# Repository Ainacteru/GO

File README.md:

# The GO flight computer
### What is this?
This repository contains the most if not all files for what is in and on the flight computer. 
### Why?
Trying to improve on working on the hardware design of embedded systems, and also learning Rust at the same time
### About the board:
Hardware:
* MCU: ATSAMD21G18A-AU
* IMU: BMI323
* Barometer: BMP390
* Flash: W25Q16JVSSIQ
* Radio: Wio-SX1262
* Buzzer
* RGB Led
* 3 Servo Ports
* 2 Pyro Channels
* USB-C
* Micro-SD card reader

Runs off of the [Microsoft UF2-SAMDx1](https://github.com/microsoft/uf2-samdx1) UF2 flashing bootloader

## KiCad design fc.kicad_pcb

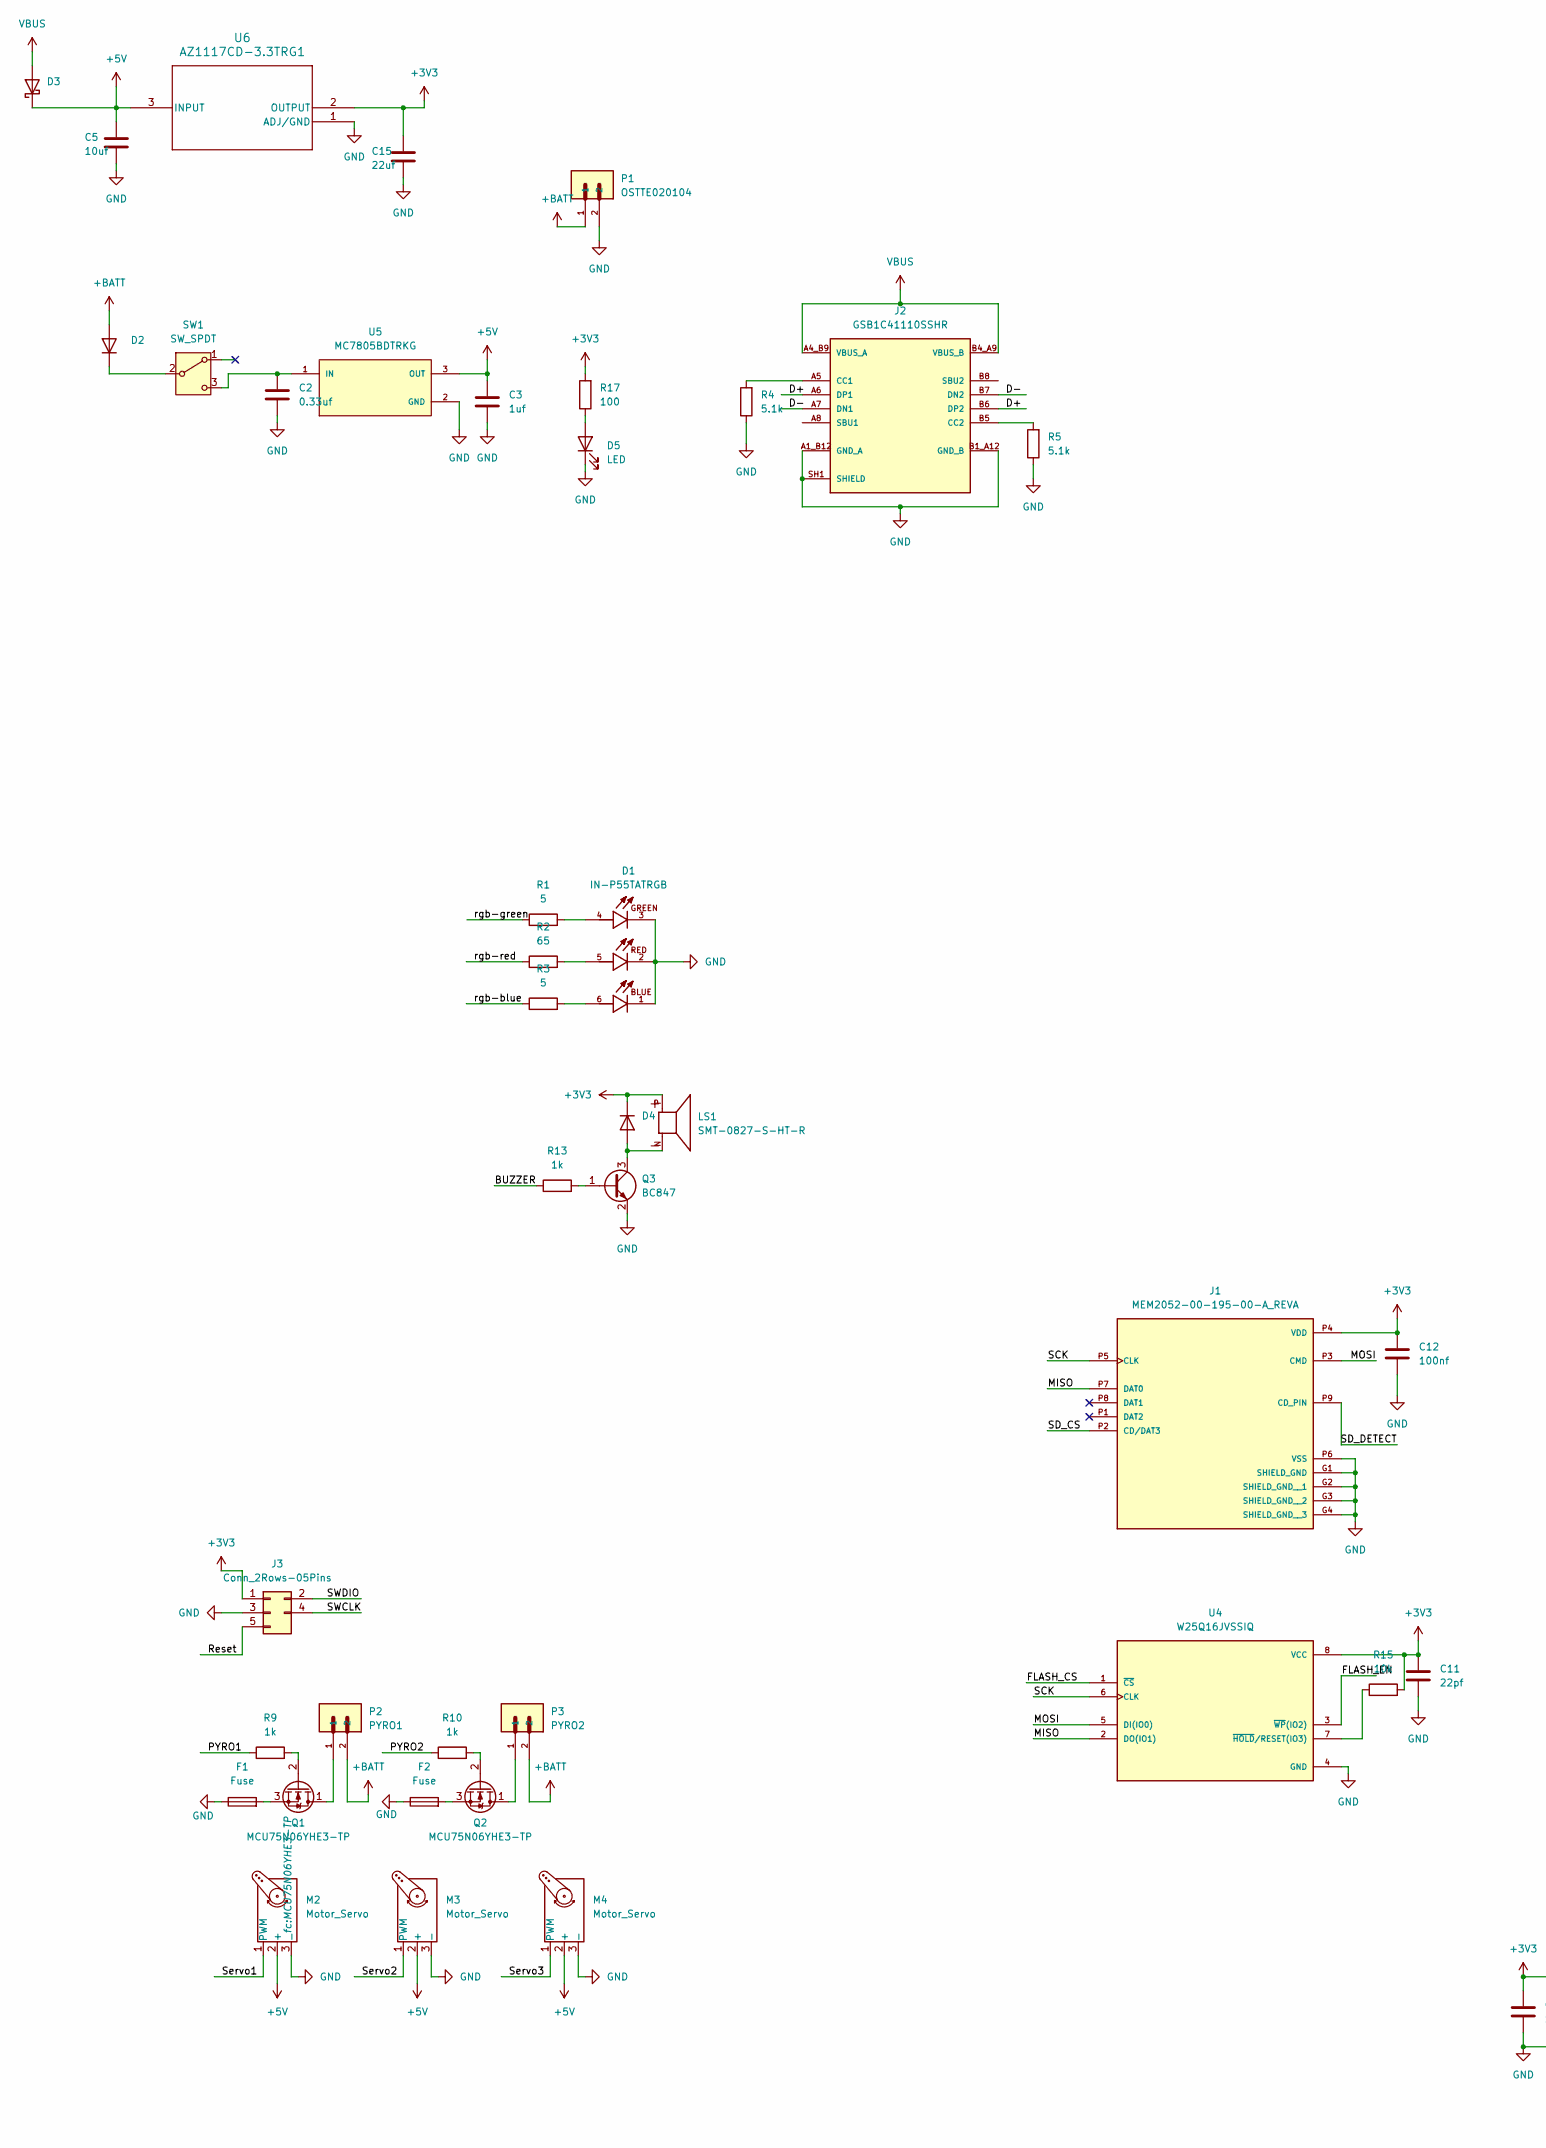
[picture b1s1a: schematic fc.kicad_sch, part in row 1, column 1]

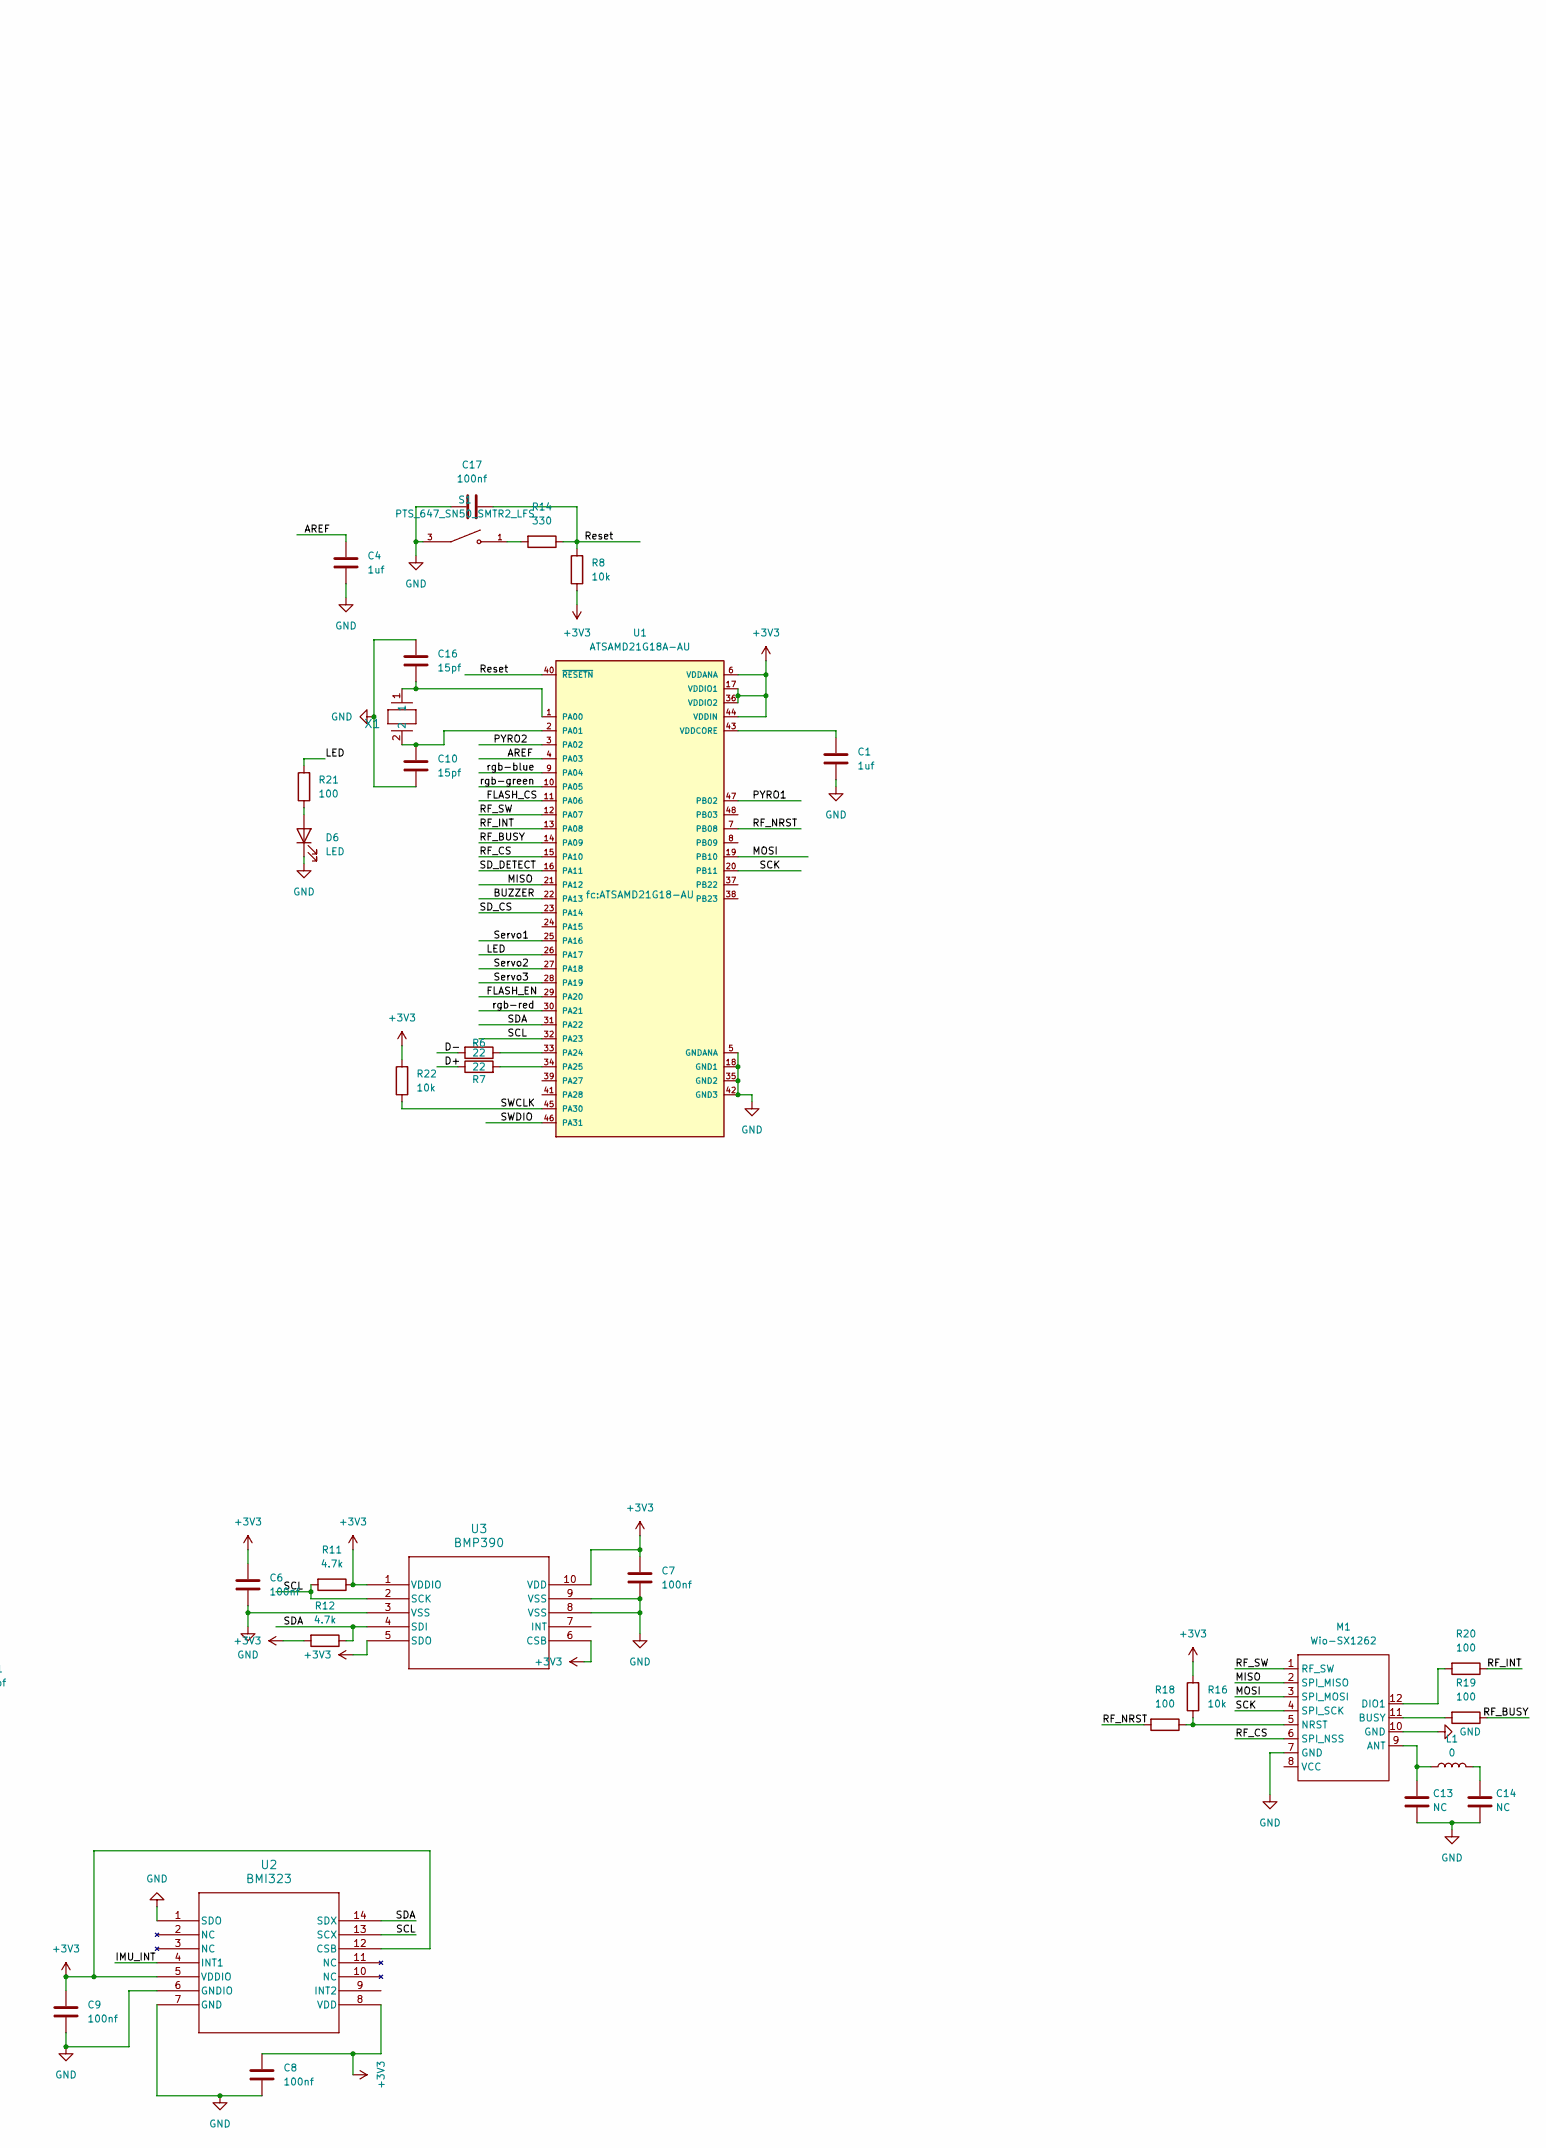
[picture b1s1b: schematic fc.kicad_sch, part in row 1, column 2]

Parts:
C1, C3, C4: 1uf; 0603-cap
C2: 0.33uf; 0603-cap
C5: 10uf; 0603-cap
C6, C7, C8, C9, C12, C17: 100nf; 0603-cap
C10, C16: 15pf; 0603-cap
C11: 22pf; 0603-cap
C13, C14: NC; C_0402_1005Metric
C15: 22uf; 0603-cap
D1: IN-P55TATRGB; LED_IN-P55TATRGB; PARTREV 1.0
D2, D3, D4: D_SOD-123
D5, D6: LED; LED_0603_1608Metric
F1, F2: Fuse; Fuse_0603_1608Metric
J1: MEM2052-00-195-00-A_REVA; GCT_MEM2052-00-195-00-A_REVA; PARTREV A
J2: GSB1C41110SSHR; AMPHENOL_GSB1C41110SSHR; PARTREV AX1; DigiKey_Part_Number 664-GSB1C41110SSHRCT-ND
J3: Conn_2Rows-05Pins; PinSocket_2x03_odd
L1: 0; L_0402_1005Metric
LS1: SMT-0827-S-HT-R; XDCR_SMT-0827-S-HT-R; PARTREV 31/03/20
M1: Wio-SX1262
M2, M3, M4: Motor_Servo; PinHeader_1x03_P2.54mm_Vertical
P1: OSTTE020104; OST_OSTTE020104
P2: PYRO1; OST_OSTTE020104
P3: PYRO2; OST_OSTTE020104
Q1, Q2: MCU75N06YHE3-TP
Q3: BC847; SOT-23
R1, R3: 5; R_0603_1608Metric
R2: 65; R_0603_1608Metric
R4, R5: 5.1k; R_0603_1608Metric
R6, R7: 22; R_0603_1608Metric
R8, R15, R16, R22: 10k; R_0603_1608Metric
R9, R10, R13: 1k; R_0603_1608Metric
R11, R12: 4.7k; R_0603_1608Metric
R14: 330; R_0603_1608Metric
R17, R18, R19, R20, R21: 100; R_0603_1608Metric
S1: PTS_647_SN50_SMTR2_LFS; SW_PTS_647_SN50_SMTR2_LFS; PARTREV 4 Apr 22
SW1: SW_SPDT; SW_OS102011MS2QN1
U1: ATSAMD21G18A-AU; ATSAMD21G18-AU
U2: BMI323; BMI323_BOS
U3: BMP390
U4: W25Q16JVSSIQ
U5: MC7805BDTRKG; DPAK229P990X238-4N; PARTREV 27
U6: AZ1117CD-3.3TRG1; TO252-2-3.3V_DIO
X1: FC-135 32.7680KA-A5; XTAL_FC-135_EPS

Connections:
+3V3: C6.1, C7.1, C8.1, C9.1, C11.1, C12.1, C15.1, D4.1 (K), J1.P4 (VDD), J3.1, LS1.P, R8.1, R11.1, R12.2, R15.2, R16.2, R17.2, R22.2, U1.6 (VDDANA), U1.17 (VDDIO1), U1.36 (VDDIO2), U1.44 (VDDIN), U2.5 (VDDIO), U2.8 (VDD), U2.12 (CSB), U3.1 (VDDIO), U3.5 (SDO), U3.6 (CSB), U3.10 (VDD), U4.8 (VCC), U6.2 (OUTPUT)
+5V: C3.1, C5.1, D3.1 (K), M2.2 (+), M3.2 (+), M4.2 (+), U5.3 (OUT), U6.3 (INPUT)
+BATT: D2.2 (A), P1.1, P2.2, P3.2
/AREF: C4.1, U1.4 (PA03)
/BUZZER: R13.1, U1.22 (PA13)
/FLASH_CS: U1.11 (PA06), U4.1 (~CS)
/FLASH_EN: U1.29 (PA20), U4.3 (~WP(IO2))
/IMU_INT: U2.4 (INT1)
/LED: R21.2, U1.26 (PA17)
/MISO: J1.P7 (DAT0), M1.2 (SPI_MISO), U1.21 (PA12), U4.2 (DO(IO1))
/MOSI: J1.P3 (CMD), M1.3 (SPI_MOSI), U1.19 (PB10), U4.5 (DI(IO0))
/PYRO1: R9.1, U1.47 (PB02)
/PYRO2: R10.1, U1.3 (PA02)
/RF_BUSY: R19.1, U1.14 (PA09)
/RF_CS: M1.6 (SPI_NSS), U1.15 (PA10)
/RF_INT: R20.1, U1.13 (PA08)
/RF_NRST: R18.2, U1.7 (PB08)
/RF_SW: M1.1 (RF_SW), U1.12 (PA07)
/Reset: C17.2, J3.5, R8.2, R14.1, U1.40 (~RESETN)
/SCK: J1.P5 (CLK), M1.4 (SPI_SCK), U1.20 (PB11), U4.6 (CLK)
/SCL: R11.2, U1.32 (PA23), U2.13 (SCX), U3.2 (SCK)
/SDA: R12.1, U1.31 (PA22), U2.14 (SDX), U3.4 (SDI)
/SD_CS: J1.P2 (CD/DAT3), U1.23 (PA14)
/SD_DETECT: J1.P9 (CD_PIN), U1.16 (PA11)
/SWCLK: J3.4, R22.1, U1.45 (PA30)
/SWDIO: J3.2, U1.46 (PA31)
/Servo1: M2.1 (PWM), U1.25 (PA16)
/Servo2: M3.1 (PWM), U1.27 (PA18)
/Servo3: M4.1 (PWM), U1.28 (PA19)
/rgb-blue: R3.1, U1.9 (PA04)
/rgb-green: R1.1, U1.10 (PA05)
/rgb-red: R2.1, U1.30 (PA21)
GND: C1.2, C2.2, C3.2, C4.2, C5.2, C6.2, C7.2, C8.2, C9.2, C10.1, C11.2, C12.2, C13.2, C14.2, C15.2, C16.1, C17.1, D1.1, D1.2, D1.3, D5.1 (K), D6.1 (K), F1.1, F2.1, J1.G1 (SHIELD_GND), J1.G2 (SHIELD_GND__1), J1.G3 (SHIELD_GND__2), J1.G4 (SHIELD_GND__3), J1.P6 (VSS), J2.A1_B12 (GND_A), J2.B1_A12 (GND_B), J2.SH1 (SHIELD), J2.SH2 (SHIELD), J2.SH3 (SHIELD), J2.SH4 (SHIELD), J3.3, M1.7 (GND), M1.10 (GND), M2.3 (-), M3.3 (-), M4.3 (-), P1.2, Q3.2 (E), R4.1, R5.1, S1.3, S1.4, U1.5 (GNDANA), U1.18 (GND1), U1.35 (GND2), U1.42 (GND3), U2.1 (SDO), U2.6 (GNDIO), U2.7 (GND), U3.3 (VSS), U3.8 (VSS), U3.9 (VSS), U4.4 (GND), U5.2 (GND), U6.1 (ADJ/GND)
unnamed: C14.1, L1.2
unnamed: D1.4, R1.2
unnamed: D1.5, R2.2
unnamed: D1.6, R3.2
unnamed: D2.1 (K), SW1.2 (B)
unnamed: D4.2 (A), LS1.N, Q3.3 (C)
unnamed: D5.2 (A), R17.1
unnamed: D6.2 (A), R21.1
unnamed: J2.A5 (CC1), R4.2
unnamed: J2.B5 (CC2), R5.2
unnamed: C13.1, L1.1, M1.9 (ANT)
unnamed: M1.11 (BUSY), R19.2
unnamed: M1.12 (DIO1), R20.2
unnamed: M1.5 (NRST), R16.1, R18.1
unnamed: P2.1, Q1.1 (D)
unnamed: Q1.2 (G), R9.2
unnamed: F1.2, Q1.3 (S)
unnamed: P3.1, Q2.1 (D)
unnamed: Q2.2 (G), R10.2
unnamed: F2.2, Q2.3 (S)
unnamed: Q3.1 (B), R13.2
unnamed: R14.2, S1.1, S1.2
unnamed: C2.1, SW1.3 (C), U5.1 (IN)
unnamed: C16.2, U1.1 (PA00), X1.1
unnamed: C10.2, U1.2 (PA01), X1.2
unnamed: R6.1, U1.33 (PA24)
unnamed: R7.2, U1.34 (PA25)
unnamed: C1.1, U1.43 (VDDCORE)
unnamed: R15.1, U4.7 (~HOLD/RESET(IO3))
VBUS: D3.2 (A), J2.A4_B9 (VBUS_A), J2.B4_A9 (VBUS_B)

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
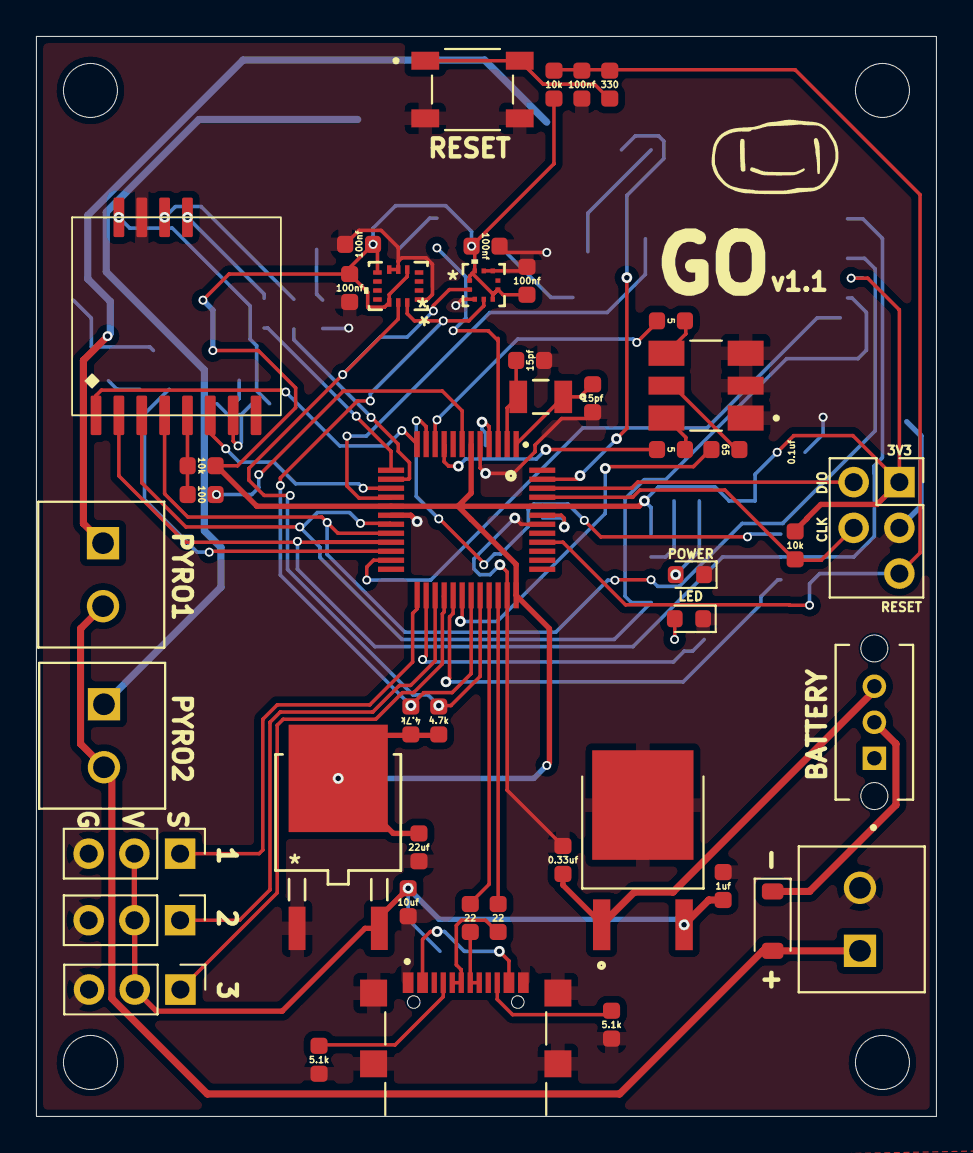
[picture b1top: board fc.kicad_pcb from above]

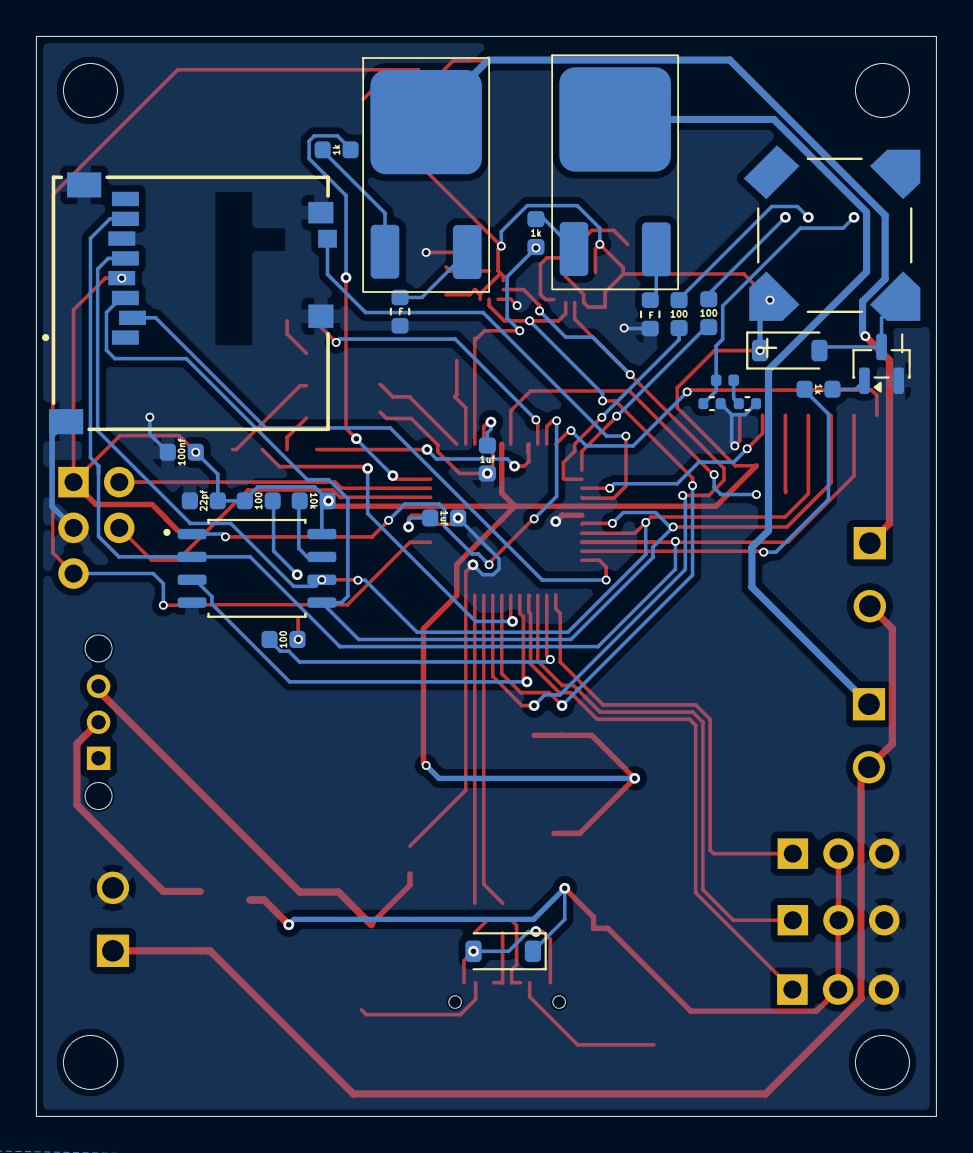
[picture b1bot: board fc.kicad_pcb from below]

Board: 2 copper layers, 50.0 x 60.0 mm, 71 parts (25 on the bottom side), 64 nets.

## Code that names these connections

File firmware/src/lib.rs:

#![no_std]


pub mod communcation;
pub mod actuators;
pub mod indicators;
pub mod sensors;
pub mod peripherals;

#[cfg(feature = "rt")]
pub use cortex_m_rt::entry;

pub use atsamd_hal as hal;
pub use hal::ehal;
pub use hal::pac;

use hal::clock::GenericClockController;
use hal::sercom::{i2c, spi};
use hal::time::Hertz;

#[cfg(feature = "usb")]
use hal::usb::{usb_device::bus::UsbBusAllocator, UsbBus};

hal::bsp_peripherals!(
    Sercom3 { I2cSercom }
    Sercom4 { SpiSercom }
);

/// Definitions related to pins and pin aliases
pub mod pins {
    use super::hal;

    hal::bsp_pins!(
        PA02 {
            /// Pyro channel 2 output
            name: pyro2
            aliases: {
                PushPullOutput: Pyro2
            }
        }
        PA03 {
            /// AREF pin - has 1uF capacitor to ground
            name: aref
        }
        PA04 {
            /// RGB LED blue channel
            name: rgb_blue
            aliases: {
                PushPullOutput: RgbBlue
                AlternateE: RgbBluePwm

            }
        }
        PA05 {
            /// RGB LED green channel
            name: rgb_green
            aliases: {
                PushPullOutput: RgbGreen
                AlternateE: RgbGreenPwm
            }
        }
        PA06 {
            /// SPI chip select for external flash
            name: flash_cs
            aliases: {
                PushPullOutput: FlashCs
            }
        }
        PA07 {
            /// RF module antenna switch
            name: rf_sw
            aliases: {
                PushPullOutput: RfSw
            }
        }
        PA08 {
            /// RF module interrupt
            name: rf_int
            aliases: {
                PullUpInput: RfInt
            }
        }
        PA09 {
            /// RF module busy signal
            name: rf_busy
            aliases: {
                PullUpInput: RfBusy
            }
        }
        PA10 {
            /// RF module chip select
            name: rf_cs
            aliases: {
                PushPullOutput: RfCs
            }
        }
        PA11 {
            /// SD card detect
            name: sd_detect
            aliases: {
                PullUpInput: SdDetect
            }
        }
        PA12 {
            /// SPI MISO
            name: miso
            aliases: {
                AlternateD: Miso
            }
        }
        PA13 {
            /// Buzzer output
            name: buzzer
            aliases: {
                PushPullOutput: Buzzer
            }
        }
        PA14 {
            /// SD card chip select
            name: sd_cs
            aliases: {
                PushPullOutput: SdCs
            }
        }
        PA16 {
            /// Servo 1 PWM output
            name: servo1
            aliases: {
                AlternateE: Servo1Pwm
            }
        }
        PA17 {
            /// Status LED
            name: led
            aliases: {
                PushPullOutput: Led
            }
        }
        PA18 {
            /// Servo 2 PWM output
            name: servo2
            aliases: {
                AlternateF: Servo2Pwm
            }
        }
        PA19 {
            /// Servo 3 PWM output
            name: servo3
            aliases: {
                AlternateF: Servo3Pwm
            }
        }
        PA20 {
            /// External flash enable
            name: flash_en
            aliases: {
                PushPullOutput: FlashEn
            }
        }
        PA21 {
            /// RGB LED red channel
            name: rgb_red
            aliases: {
                PushPullOutput: RgbRed
                AlternateF: RgbRedPwm
            }
        }
        PA22 {
            /// I2C data line
            name: sda
            aliases: {
                AlternateC: Sda
            }
        }
        PA23 {
            /// I2C clock line
            name: scl
            aliases: {
                AlternateC: Scl
            }
        }
        PA24 {
            /// USB D-
            name: usb_dm
            aliases: {
                AlternateG: UsbDm
            }
        }
        PA25 {
            /// USB D+
            name: usb_dp
            aliases: {
                AlternateG: UsbDp
            }
        }
        PB02 {
            /// Pyro channel 1 output
            name: pyro1
            aliases: {
                PushPullOutput: Pyro1
            }
        }
        PB08 {
            /// RF module reset
            name: rf_nrst
            aliases: {
                PushPullOutput: RfNrst
            }
        }
        PB10 {
            /// SPI MOSI
            name: mosi
            aliases: {
                AlternateD: Mosi
            }
        }
        PB11 {
            /// SPI SCLK
            name: sclk
            aliases: {
                AlternateD: Sclk
            }
        }
    );
}
pub use pins::*;

/// SPI pads for the labelled SPI peripheral
pub type SpiPads = spi::Pads<SpiSercom, Miso, Mosi, Sclk>;

/// SPI master for the labelled SPI peripheral
pub type Spi = spi::Spi<spi::Config<SpiPads>, spi::Duplex>;

/// Convenience for setting up the SPI peripheral (Sercom4, SPI Mode 0).
pub fn spi_master(
    clocks: &mut GenericClockController,
    baud: Hertz,
    sercom: SpiSercom,
    pm: &mut pac::Pm,
    sclk: impl Into<Sclk>,
    mosi: impl Into<Mosi>,
    miso: impl Into<Miso>,
) -> Spi {
    let gclk0 = clocks.gclk0();
    let clock = clocks.sercom4_core(&gclk0).unwrap();
    let freq = clock.freq();
    let (miso, mosi, sclk) = (miso.into(), mosi.into(), sclk.into());
    let pads = spi::Pads::default().data_in(miso).data_out(mosi).sclk(sclk);
    spi::Config::new(pm, sercom, pads, freq)
        .baud(baud)
        .spi_mode(spi::MODE_0)
        .enable()
}

/// I2C pads for the labelled I2C peripheral
pub type I2cPads = i2c::Pads<I2cSercom, Sda, Scl>;

/// I2C master for the labelled I2C peripheral
pub type I2c = i2c::I2c<i2c::Config<I2cPads>>;

/// Convenience for setting up the I2C peripheral (Sercom3).
pub fn i2c_master(
    clocks: &mut GenericClockController,
    baud: impl Into<Hertz>,
    sercom: I2cSercom,
    pm: &mut pac::Pm,
    sda: impl Into<Sda>,
    scl: impl Into<Scl>,
) -> I2c {
    let gclk0 = clocks.gclk0();
    let clock = &clocks.sercom3_core(&gclk0).unwrap();
    let freq = clock.freq();
    let baud = baud.into();
    let pads = i2c::Pads::new(sda.into(), scl.into());
    i2c::Config::new(pm, sercom, pads, freq).baud(baud).enable()
}

#[cfg(feature = "usb")]
/// Convenience function for setting up USB
pub fn usb_allocator(
    usb: pac::Usb,
    clocks: &mut GenericClockController,
    pm: &mut pac::Pm,
    dm: impl Into<UsbDm>,
    dp: impl Into<UsbDp>,
) -> UsbBusAllocator<UsbBus> {
    let gclk0 = clocks.gclk0();
    let clock = &clocks.usb(&gclk0).unwrap();
    let (dm, dp) = (dm.into(), dp.into());
    UsbBusAllocator::new(UsbBus::new(clock, pm, dm, dp, usb))
}

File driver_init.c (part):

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
	gpio_set_pin_function(SERVO_1, PINMUX_PA16F_TCC0_WO6);

	gpio_set_pin_function(BUZZER, PINMUX_PA13F_TCC0_WO7);
}

void PWM_0_CLOCK_init(void)
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{
	init_mcu();

	// GPIO on PA02

	gpio_set_pin_level(PYRO_2,
	                   // <y> Initial level
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
	gpio_set_pin_function(PYRO_2, GPIO_PIN_FUNCTION_OFF);

	// GPIO on PA04

	gpio_set_pin_level(PYRO_1,
	                   // <y> Initial level
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
	gpio_set_pin_function(PYRO_1, GPIO_PIN_FUNCTION_OFF);

	// GPIO on PA05

	gpio_set_pin_level(RF_NRST,
	                   // <y> Initial level
	                   // <id> pad_initial_level
	                   // <false"> Low
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	                   true);

	// Set pin direction to output
	gpio_set_pin_direction(RF_NRST, GPIO_DIRECTION_OUT);

	gpio_set_pin_function(RF_NRST, GPIO_PIN_FUNCTION_OFF);

	// GPIO on PA07

	gpio_set_pin_level(RF_SW,
	                   // <y> Initial level
	                   // <id> pad_initial_level
	                   // <false"> Low
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	                   false);

	// Set pin direction to output
	gpio_set_pin_direction(RF_SW, GPIO_DIRECTION_OUT);

	gpio_set_pin_function(RF_SW, GPIO_PIN_FUNCTION_OFF);

	// GPIO on PA08

	// Set pin direction to input
	gpio_set_pin_direction(RF_INT, GPIO_DIRECTION_IN);

	gpio_set_pin_pull_mode(RF_INT,
	                       // <y> Pull configuration
	                       // <id> pad_pull_config
	                       // <GPIO_PULL_OFF"> Off
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	                       // <GPIO_PULL_DOWN"> Pull-down
	                       GPIO_PULL_OFF);

	gpio_set_pin_function(RF_INT, GPIO_PIN_FUNCTION_OFF);

	// GPIO on PA09

	// Set pin direction to input
	gpio_set_pin_direction(RF_BUSY, GPIO_DIRECTION_IN);

	gpio_set_pin_pull_mode(RF_BUSY,
	                       // <y> Pull configuration
	                       // <id> pad_pull_config
	                       // <GPIO_PULL_OFF"> Off
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	                       // <GPIO_PULL_DOWN"> Pull-down
	                       GPIO_PULL_OFF);

	gpio_set_pin_function(RF_BUSY, GPIO_PIN_FUNCTION_OFF);

	// GPIO on PA10

	gpio_set_pin_level(RF_CS,
	                   // <y> Initial level
	                   // <id> pad_initial_level
	                   // <false"> Low
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	                   true);

	// Set pin direction to output
	gpio_set_pin_direction(RF_CS, GPIO_DIRECTION_OUT);

	gpio_set_pin_function(RF_CS, GPIO_PIN_FUNCTION_OFF);

	// GPIO on PA11

	// Set pin direction to input
	gpio_set_pin_direction(SD_DETECT, GPIO_DIRECTION_IN);

	gpio_set_pin_pull_mode(SD_DETECT,
	                       // <y> Pull configuration
	                       // <id> pad_pull_config
	                       // <GPIO_PULL_OFF"> Off
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	                       // <GPIO_PULL_DOWN"> Pull-down
	                       GPIO_PULL_OFF);

	gpio_set_pin_function(SD_DETECT, GPIO_PIN_FUNCTION_OFF);

	// GPIO on PA14

	gpio_set_pin_level(SD_CS,
	                   // <y> Initial level
	                   // <id> pad_initial_level
	                   // <false"> Low
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	                   true);

	// Set pin direction to output
	gpio_set_pin_direction(SD_CS, GPIO_DIRECTION_OUT);

	gpio_set_pin_function(SD_CS, GPIO_PIN_FUNCTION_OFF);

	// GPIO on PA15

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
	gpio_set_pin_function(BMP_INT, GPIO_PIN_FUNCTION_OFF);

	// GPIO on PA17

	gpio_set_pin_level(FLASH_CS,
	                   // <y> Initial level
	                   // <id> pad_initial_level
	                   // <false"> Low
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	                   true);

	// Set pin direction to output
	gpio_set_pin_direction(FLASH_CS, GPIO_DIRECTION_OUT);

	gpio_set_pin_function(FLASH_CS, GPIO_PIN_FUNCTION_OFF);

	// GPIO on PA21

	// Set pin direction to input
	gpio_set_pin_direction(IMU_INT, GPIO_DIRECTION_IN);
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
	gpio_set_pin_function(IMU_INT, GPIO_PIN_FUNCTION_OFF);

	// GPIO on PB02

	gpio_set_pin_level(RGB_RED,
	                   // <y> Initial level
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
	gpio_set_pin_function(RGB_RED, GPIO_PIN_FUNCTION_OFF);

	// GPIO on PB08

	gpio_set_pin_level(RGB_BLUE,
	                   // <y> Initial level
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
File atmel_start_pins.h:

/*
 * Code generated from Atmel Start.
 *
 * This file will be overwritten when reconfiguring your Atmel Start project.
 * Please copy examples or other code you want to keep to a separate file
 * to avoid losing it when reconfiguring.
 */
#ifndef ATMEL_START_PINS_H_INCLUDED
#define ATMEL_START_PINS_H_INCLUDED

#include <hal_gpio.h>

// SAMD21 has 8 pin functions

#define GPIO_PIN_FUNCTION_A 0
#define GPIO_PIN_FUNCTION_B 1
#define GPIO_PIN_FUNCTION_C 2
#define GPIO_PIN_FUNCTION_D 3
#define GPIO_PIN_FUNCTION_E 4
#define GPIO_PIN_FUNCTION_F 5
#define GPIO_PIN_FUNCTION_G 6
#define GPIO_PIN_FUNCTION_H 7

#define PA00 GPIO(GPIO_PORTA, 0)
#define PA01 GPIO(GPIO_PORTA, 1)
#define PYRO_2 GPIO(GPIO_PORTA, 2)
#define PYRO_1 GPIO(GPIO_PORTA, 4)
#define RF_NRST GPIO(GPIO_PORTA, 5)
#define RF_SW GPIO(GPIO_PORTA, 7)
#define RF_INT GPIO(GPIO_PORTA, 8)
#define RF_BUSY GPIO(GPIO_PORTA, 9)
#define RF_CS GPIO(GPIO_PORTA, 10)
#define SD_DETECT GPIO(GPIO_PORTA, 11)
#define MISO GPIO(GPIO_PORTA, 12)
#define BUZZER GPIO(GPIO_PORTA, 13)
#define SD_CS GPIO(GPIO_PORTA, 14)
#define BMP_INT GPIO(GPIO_PORTA, 15)
#define SERVO_1 GPIO(GPIO_PORTA, 16)
#define FLASH_CS GPIO(GPIO_PORTA, 17)
#define SERVO_2 GPIO(GPIO_PORTA, 18)
#define SERVO_3 GPIO(GPIO_PORTA, 19)
#define IMU_INT GPIO(GPIO_PORTA, 21)
#define SDA GPIO(GPIO_PORTA, 22)
#define SCL GPIO(GPIO_PORTA, 23)
#define PA30 GPIO(GPIO_PORTA, 30)
#define RGB_RED GPIO(GPIO_PORTB, 2)
#define RGB_BLUE GPIO(GPIO_PORTB, 8)
#define RGB_GREEN GPIO(GPIO_PORTB, 9)
#define MOSI GPIO(GPIO_PORTB, 10)
#define SCK GPIO(GPIO_PORTB, 11)

#endif // ATMEL_START_PINS_H_INCLUDED

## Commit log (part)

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2026-03-19 init help nothing makes sense
2026-03-19 new config
2026-03-19 Revert "new config"
2026-03-20 starting to organize
2026-03-20 removing build files
2026-03-20 pwm config set up
2026-05-14 code
2026-05-14 Add additional directories to .gitignore
2026-05-16 trying servo code but rust is kinda hard
2026-05-17 servo works and starting led stuff
2026-05-18 rgb led stuff works almost just need to change clock channels, also cool panic handler! also tested servos
2026-05-18 Update README with PDF link and image
    Added a PDF link and an image to the README.
2026-05-18 Update README to include images instead of PDF link
    Replaced PDF link with an image.
2026-05-19 read me because i can't code
2026-05-22 trying to read temperatures
2026-05-22 completed temperature, pressure and altitude readings, however the numbers are off by a little bit
2026-05-22 baro is very jittery so gonna try to turn on oversampling and iir, maybe a filter if that doesnt help enough
2026-05-23 Added new structuer
2026-06-14 using the blocking version of the bmp that i wrote instead of a crate also added defmt from the other repo and it works now just need to work on recieving messages
2026-06-15 you can toggle the led by typing 'led' over usb to it but i can't get it to work over rust only tio so i'm confused
2026-06-19 more stuff
2026-06-20 YAY BAROMETER READING USING ASYNC
2026-06-20 Remove output binaries, update .gitignore
2026-06-23 imu and barometer now work!
2026-06-24 buzzer! and hot cross buns
2026-06-26 somehow implemented flash turns out i just had to slather solder paste everywhere to fix the issue
